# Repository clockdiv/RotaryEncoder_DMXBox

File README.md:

# RotaryEncoder_DMXBox
a small machine with rotary encoders to controll DMX devices

* PCB created in KiCad 5.1.9
* Code written in vscode with PlatformIO
* based on the Teensy 3.2 Project by pjrc.com

## Basic function
The values of the rotary encoders are mapped to specific DMX channels. The idea is to create a device for interactive stages like e.g. a pully hanging from the ceiling to control moving lights or similiar with it.

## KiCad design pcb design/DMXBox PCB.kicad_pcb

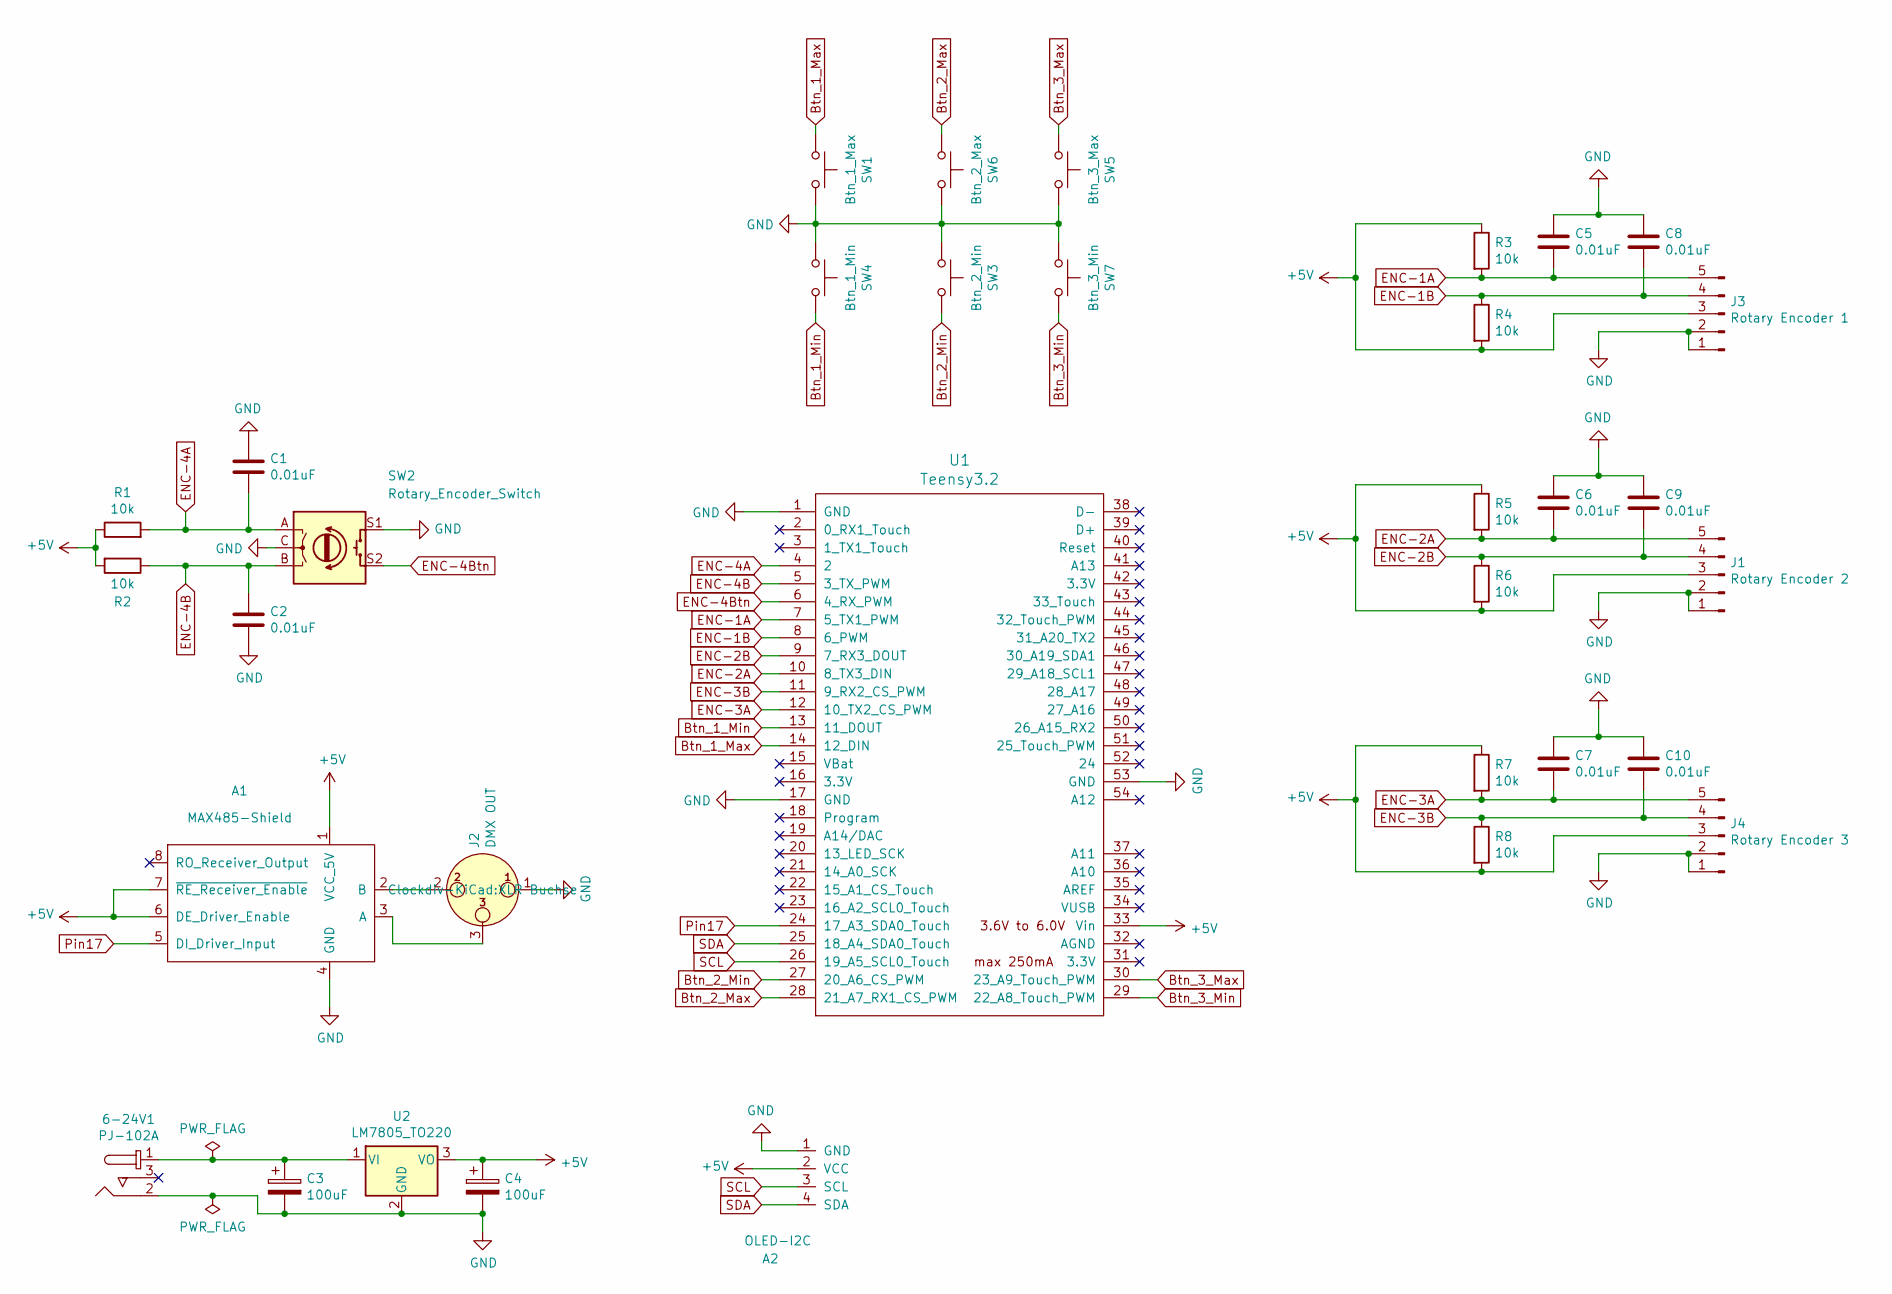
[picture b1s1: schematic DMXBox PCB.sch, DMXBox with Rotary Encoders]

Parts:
6-24V1: PJ-102A; Barrel_Jack_5.5mmODx2.1mmID_PJ-102A; MPN PJ-102A; Digi-Key_PN CP-102A-ND
A1: MAX485-Shield
A2: OLED-I2C
C1, C2, C5, C6, C7, C8, C9, C10: 0.01uF; C_0603_1608Metric_Pad1.08x0.95mm_HandSolder
C3, C4: 100uF; CP_Radial_D5.0mm_P2.50mm
J1: Rotary Encoder 2; JST_EH_B5B-EH-A_1x05_P2.50mm_Vertical
J2: DMX OUT; XLR Buchse
J3: Rotary Encoder 1; JST_EH_B5B-EH-A_1x05_P2.50mm_Vertical
J4: Rotary Encoder 3; JST_EH_B5B-EH-A_1x05_P2.50mm_Vertical
R1, R2, R3, R4, R5, R6, R7, R8: 10k; R_0603_1608Metric_Pad0.98x0.95mm_HandSolder
SW1: Btn_1_Max; CherryMX_PCBmount_NoDiodeNoLED
SW2: Rotary_Encoder_Switch; RotaryEncoder_Alps_EC11E-Switch_Vertical_H20mm_CircularMoun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
SW3: Btn_2_Min; CherryMX_PCBmount_NoDiodeNoLED
SW4: Btn_1_Min; CherryMX_PCBmount_NoDiodeNoLED
SW5: Btn_3_Max; CherryMX_PCBmount_NoDiodeNoLED
SW6: Btn_2_Max; CherryMX_PCBmount_NoDiodeNoLED
SW7: Btn_3_Min; CherryMX_PCBmount_NoDiodeNoLED
U1: Teensy3.2; Teensy30_31_32_All_Pins
U2: LM7805_TO220; TO-220-3_Vertical

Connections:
+5V: A1.1 (VCC_5V), A1.6 (DE_Driver_Enable), A1.7 (~RE_Receiver_Enable), A2.2 (VCC), C4.1, J1.3, J3.3, J4.3, R1.1, R2.2, R3.1, R4.2, R5.1, R6.2, R7.1, R8.2, U1.33 (Vin), U2.3 (VO)
Btn_1_Max: SW1.1, U1.14 (12_DIN)
Btn_1_Min: SW4.2, U1.13 (11_DOUT)
Btn_2_Max: SW6.1, U1.28 (21_A7_RX1_CS_PWM)
Btn_2_Min: SW3.2, U1.27 (20_A6_CS_PWM)
Btn_3_Max: SW5.1, U1.30 (23_A9_Touch_PWM)
Btn_3_Min: SW7.2, U1.29 (22_A8_Touch_PWM)
ENC-1A: C5.2, J3.5, R3.2, U1.7 (5_TX1_PWM)
ENC-1B: C8.2, J3.4, R4.1, U1.8 (6_PWM)
ENC-2A: C6.2, J1.5, R5.2, U1.10 (8_TX3_DIN)
ENC-2B: C9.2, J1.4, R6.1, U1.9 (7_RX3_DOUT)
ENC-3A: C7.2, J4.5, R7.2, U1.12 (10_TX2_CS_PWM)
ENC-3B: C10.2, J4.4, R8.1, U1.11 (9_RX2_CS_PWM)
ENC-4A: C1.2, R1.2, SW2.A, U1.4 (2)
ENC-4B: C2.1, R2.1, SW2.B, U1.5 (3_TX_PWM)
ENC-4Btn: SW2.S2, U1.6 (4_RX_PWM)
GND: 6-24V1.2, A1.4 (GND), A2.1 (GND), C1.1, C2.2, C3.2, C4.2, C5.1, C6.1, C7.1, C8.1, C9.1, C10.1, J1.1, J1.2, J2.1, J3.1, J3.2, J4.1, J4.2, SW1.2, SW2.C, SW2.S1, SW3.1, SW4.1, SW5.2, SW6.2, SW7.1, U1.1 (GND), U1.17 (GND), U1.53 (GND), U2.2 (GND)
unnamed: 6-24V1.1, C3.1, U2.1 (VI)
unnamed: A1.2 (B), J2.2
unnamed: A1.3 (A), J2.3
Pin17: A1.5 (DI_Driver_Input), U1.24 (17_A3_SDA0_Touch)
SCL: A2.3 (SCL), U1.26 (19_A5_SCL0_Touch)
SDA: A2.4 (SDA), U1.25 (18_A4_SDA0_Touch)

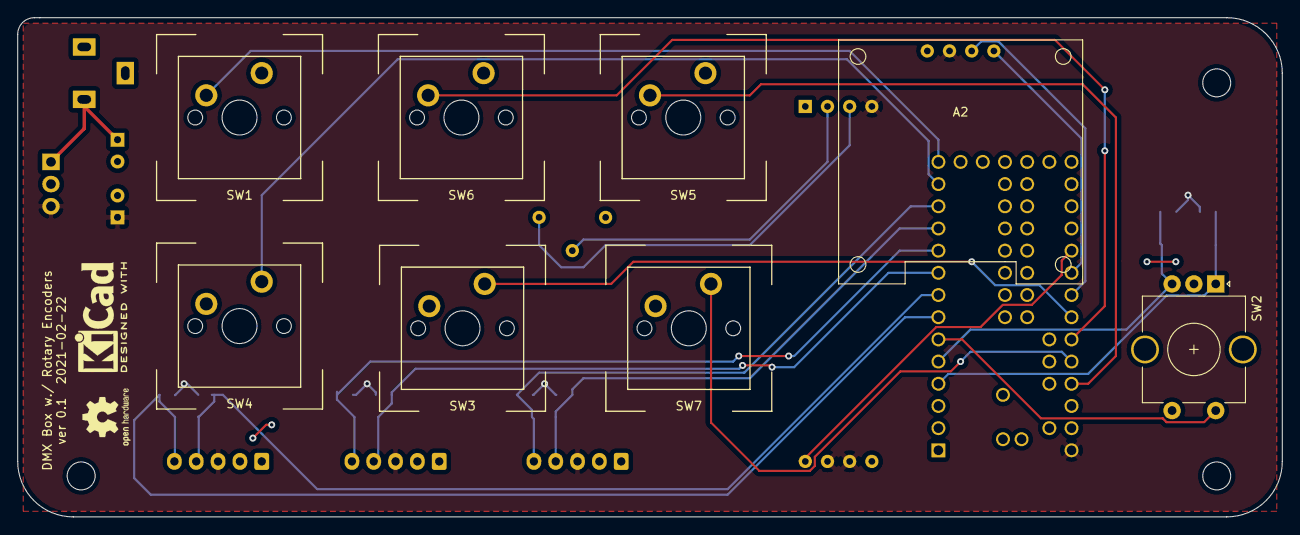
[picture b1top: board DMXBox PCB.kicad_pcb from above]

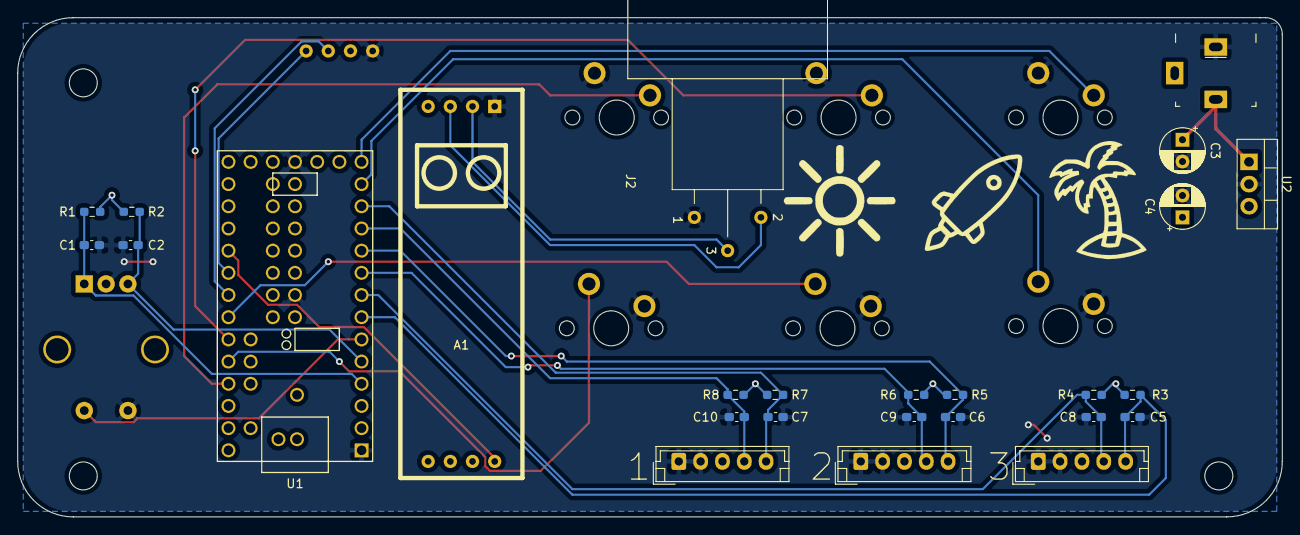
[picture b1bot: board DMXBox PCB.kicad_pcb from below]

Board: 2 copper layers, 144.8 x 57.2 mm, 34 parts (26 on the bottom side), 23 nets.

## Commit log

2021-02-24 initial commit hardware design
2021-02-24 initial commit code
2022-06-16 rebuild
    rebuild most of the code:
    - encoder on z-axis sends value to Serial
2022-06-30 clamped axis
    added a variable for a clamped axis value
